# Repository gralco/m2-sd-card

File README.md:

# m2-sd-card

M.2 Key E MicroSD card board for the Librem 5. Using a NXP NVT4857UK, TI TXS0206, Diodes Inc. PI4ULS3V4857 SD 3.0-SDR104 compliant bidirectional level translator.

The contents of this repo is licensed under the GNU GPLv3+

### Manufacturing details

The board should be 0.8mm thick. Make sure you select the "Gold fingers" option when ordering.

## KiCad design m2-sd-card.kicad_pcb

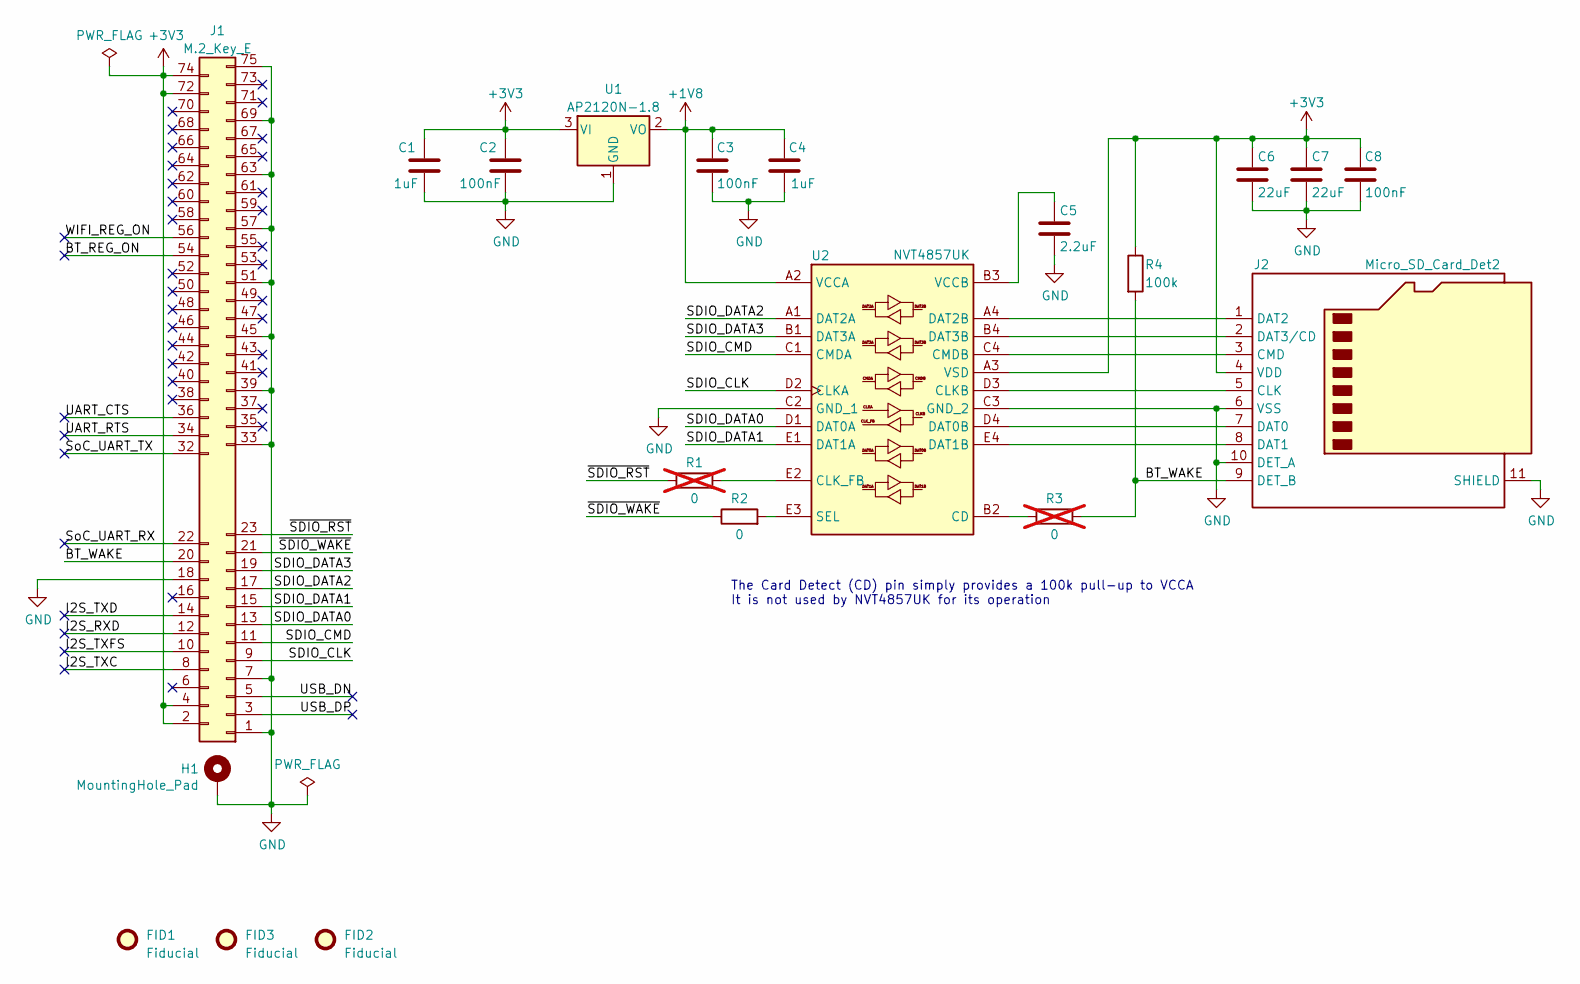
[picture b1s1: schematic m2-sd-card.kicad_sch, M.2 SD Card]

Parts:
C1, C4: 1uF; C_0402_1005Metric; Tolerance 10%; MFG Part Num CL05A105KO5NNNC
C2, C3, C8: 100nF; C_0402_1005Metric; Tolerance 10%; MFG Part Num CL05A104KA5NNNC
C5: 2.2uF; C_0402_1005Metric; Tolerance 20%; MFG Part Num CL05A225MQ5NNNC
C6, C7: 22uF; C_0402_1005Metric; Tolerance 20%; MFG Part Num CM05X5R226M06AH080
FID1, FID2, FID3: Fiducial; Fiducial_0.5mm_Mask1mm
H1: MountingHole_Pad; M.2_Mounting_Hole
J1: M.2_Key_E; M.2_Key_E_Gold_Fingers
J2: Micro_SD_Card_Det2; microSD_HC_Hirose_DM3AT-SF-PEJM5; MFG Part Num DM3AT-SF-PEJM5
R1, R3: 0; R_0402_1005Metric; MFG Part Num CRCW04020000Z0EDC; not fitted
R2: 0; R_0402_1005Metric; MFG Part Num CRCW04020000Z0EDC
R4: 100k; R_0402_1005Metric; Tolerance 1%; MFG Part Num ERJ-2RKF1003X
U1: AP2120N-1.8; SOT-23; MFG Part Num AP2120N-1.8TRG1
U2: NVT4857UK; MFG Part Num NVT4857UKAZ

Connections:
+1V8: C3.1, C4.1, U1.2 (VO), U2.A2 (VCCA)
+3V3: C1.1, C2.1, C6.1, C7.1, C8.1, J1.2, J1.4, J1.72, J1.74, J2.4 (VDD), R4.1, U1.3 (VI), U2.A3 (VSD)
/BT_REG_ON: J1.54
/BT_WAKE: J1.20, J2.9 (DET_B), R3.2, R4.2
/I2S_RXD: J1.12
/I2S_TXC: J1.8
/I2S_TXD: J1.14
/I2S_TXFS: J1.10
/SDIO_CLK: J1.9, U2.D2 (CLKA)
/SDIO_CMD: J1.11, U2.C1 (CMDA)
/SDIO_DATA0: J1.13, U2.D1 (DAT0A)
/SDIO_DATA1: J1.15, U2.E1 (DAT1A)
/SDIO_DATA2: J1.17, U2.A1 (DAT2A)
/SDIO_DATA3: J1.19, U2.B1 (DAT3A)
/SoC_UART_RX: J1.22
/SoC_UART_TX: J1.32
/UART_CTS: J1.36
/UART_RTS: J1.34
/USB_DN: J1.5
/USB_DP: J1.3
/WIFI_REG_ON: J1.56
/~SDIO_RST: J1.23, R1.1
/~SDIO_WAKE: J1.21, R2.1
GND: C1.2, C2.2, C3.2, C4.2, C5.2, C6.2, C7.2, C8.2, H1.1, J1.1, J1.7, J1.18, J1.33, J1.39, J1.45, J1.51, J1.57, J1.63, J1.69, J1.75, J2.6 (VSS), J2.10 (DET_A), J2.11 (SHIELD), U1.1 (GND), U2.C2 (GND_1), U2.C3 (GND_2)
unnamed: J2.5 (CLK), U2.D3 (CLKB)
unnamed: J2.3 (CMD), U2.C4 (CMDB)
unnamed: J2.7 (DAT0), U2.D4 (DAT0B)
unnamed: J2.8 (DAT1), U2.E4 (DAT1B)
unnamed: J2.1 (DAT2), U2.A4 (DAT2B)
unnamed: J2.2 (DAT3/CD), U2.B4 (DAT3B)
unnamed: R3.1, U2.B2 (CD)
unnamed: R1.2, U2.E2 (CLK_FB)
unnamed: R2.2, U2.E3 (SEL)
unnamed: C5.1, U2.B3 (VCCB)

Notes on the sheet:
The Card Detect (CD) pin simply provides a 100k pull-up to VCCA It is not used by NVT4857UK for its operation

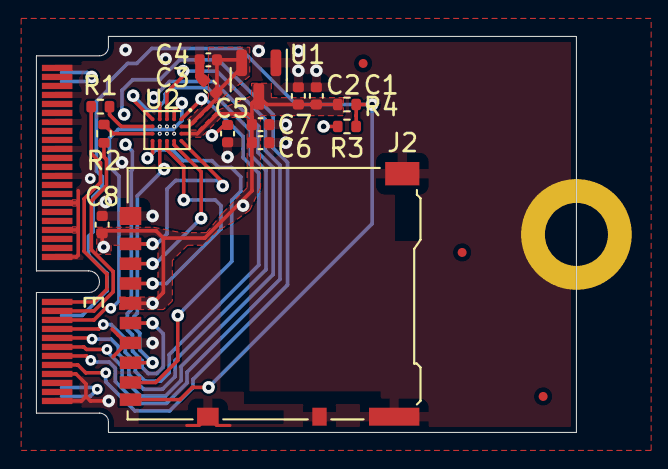
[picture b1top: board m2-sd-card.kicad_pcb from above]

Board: 4 copper layers, 30.0 x 22.0 mm, 20 parts (0 on the bottom side), 22 nets.

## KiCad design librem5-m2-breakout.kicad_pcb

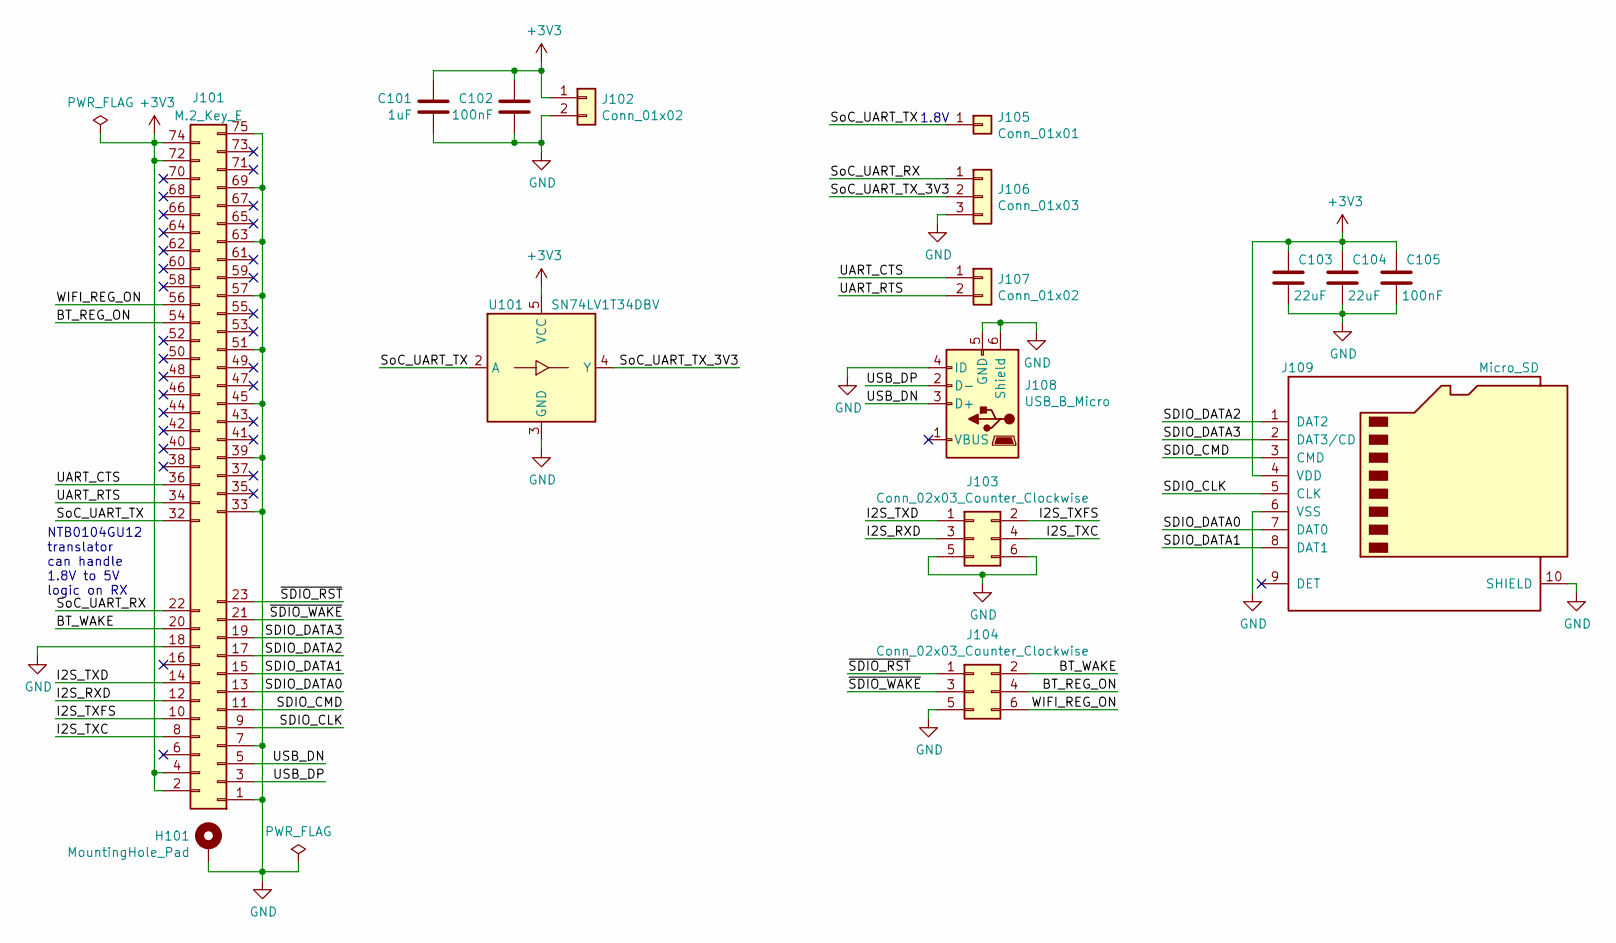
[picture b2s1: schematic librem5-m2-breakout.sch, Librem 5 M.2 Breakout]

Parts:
C101: 1uF; C_0603_1608Metric_Pad1.05x0.95mm_HandSolder
C102, C105: 100nF; C_0603_1608Metric_Pad1.05x0.95mm_HandSolder
C103, C104: 22uF; C_0603_1608Metric_Pad1.05x0.95mm_HandSolder
H101: MountingHole_Pad; M.2_Mounting_Hole
J101: M.2_Key_E; M.2_Key_E_Gold_Fingers
J102: Conn_01x02; PinHeader_1x02_P2.54mm_Vertical; MFG Part Num M20-9990246
J103, J104: Conn_02x03_Counter_Clockwise; PinHeader_2x03_P1.27mm_Vertical_SMD; MFG Part Num 54202-G08-03
J105: Conn_01x01; PinHeader_1x01_P2.54mm_Vertical; MFG Part Num 68000-401HLF
J106: Conn_01x03; PinHeader_1x03_P2.54mm_Vertical; MFG Part Num 61300311121
J107: Conn_01x02; PinHeader_1x02_P1.27mm_Vertical_SMD_Pin1Right
J108: USB_B_Micro; USB_Micro-B_Wuerth_614105150721_Vertical; MFG Part Num 47346-0001
J109: Micro_SD; ALPS_SCHA4B0419; MFG Part Num SCHA4B0419
U101: SN74LV1T34DBV; SOT-23-5_HandSoldering; MFG Part Num SN74LV1T34DBVR

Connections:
+3V3: C101.2, C102.2, C103.2, C104.2, C105.2, J101.2, J101.4, J101.72, J101.74, J102.1, J109.4 (VDD), U101.5 (VCC)
/BT_REG_ON: J101.54, J104.4
/BT_WAKE: J101.20, J104.2
/I2S_RXD: J101.12, J103.3
/I2S_TXC: J101.8, J103.4
/I2S_TXD: J101.14, J103.1
/I2S_TXFS: J101.10, J103.2
/SDIO_CLK: J101.9, J109.5 (CLK)
/SDIO_CMD: J101.11, J109.3 (CMD)
/SDIO_DATA0: J101.13, J109.7 (DAT0)
/SDIO_DATA1: J101.15, J109.8 (DAT1)
/SDIO_DATA2: J101.17, J109.1 (DAT2)
/SDIO_DATA3: J101.19, J109.2 (DAT3/CD)
/SoC_UART_RX: J101.22, J106.1
/SoC_UART_TX: J101.32, J105.1, U101.2 (A)
/SoC_UART_TX_3V3: J106.2, U101.4 (Y)
/UART_CTS: J101.36, J107.1
/UART_RTS: J101.34, J107.2
/USB_DN: J101.5, J108.3 (D+)
/USB_DP: J101.3, J108.2 (D-)
/WIFI_REG_ON: J101.56, J104.6
/~SDIO_RST: J101.23, J104.1
/~SDIO_WAKE: J101.21, J104.3
GND: C101.1, C102.1, C103.1, C104.1, C105.1, H101.1, J101.1, J101.7, J101.18, J101.33, J101.39, J101.45, J101.51, J101.57, J101.63, J101.69, J101.75, J102.2, J103.5, J103.6, J104.5, J106.3, J108.4 (ID), J108.5 (GND), J108.6 (Shield), J109.6 (VSS), J109.10 (SHIELD), U101.3 (GND)

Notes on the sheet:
NTB0104GU12 translator can handle 1.8V to 5V logic on RX
1.8V

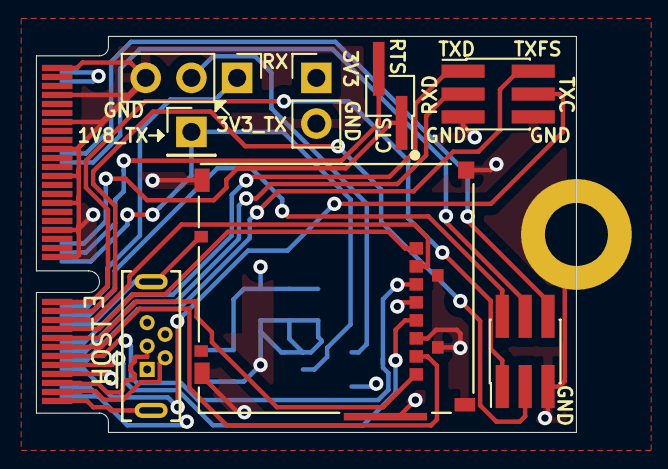
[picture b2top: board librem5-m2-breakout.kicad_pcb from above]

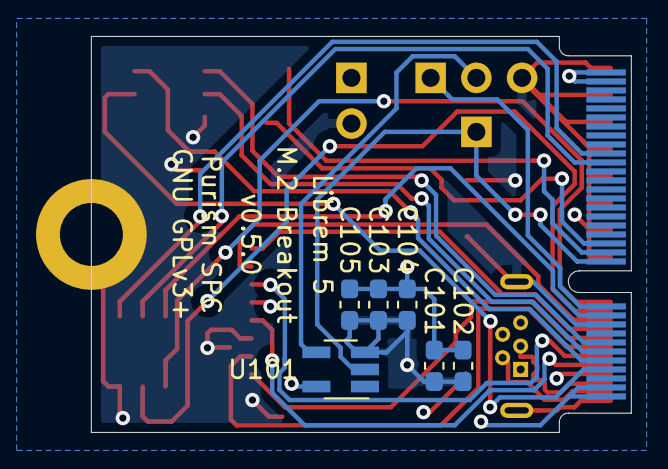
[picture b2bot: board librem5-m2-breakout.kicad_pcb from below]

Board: 4 copper layers, 30.0 x 22.0 mm, 16 parts (6 on the bottom side), 24 nets.

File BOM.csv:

Reference, Value, Footprint, Datasheet, Distrib Link, Distrib PN, MFG Name, MFG Part Num, Others, Tolerance
J102,Conn_01x02,Connector_PinHeader_2.54mm:PinHeader_1x02_P2.54mm_Vertical,~,https://www.digikey.com/product-detail/en/harwin-inc/M20-999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,952-2262-ND,Harwin,M20-9990246,https://www.digikey.com/products/en/connectors-interconnects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,-
C102,100nF,Capacitor_SMD:C_0603_1608Metric_Pad1.05x0.95mm_HandSolder,~,,,,,,
U101,SN74LV1T34DBV,Package_TO_SOT_SMD:SOT-23-5_HandSoldering,http://www.ti.com/lit/ds/symlink/sn74lv1t34.pdf,https://www.digikey.com/product-detail/en/texas-instruments/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,296-37176-1-ND,TI,SN74LV1T34DBVR,https://octopart.com/search?q=SN74LV1T34DBV,-
J109,Micro_SD,m2-sd-card:ALPS_SCHA4B0419,https://www.mouser.com/datasheet/2/15/alps_SCHA4B0419-1155906.pdf,https://www.mouser.com/ProductDetail/ALPS/SCHA4B0419?qs=sGAE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,688-SCHA4B0419,ALPS,SCHA4B0419,https://www.mouser.com/Connectors/Memory-Connectors/Memory-C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|0,-
C105,100nF,Capacitor_SMD:C_0603_1608Metric_Pad1.05x0.95mm_HandSolder,~,,,,,,
C104,22uF,Capacitor_SMD:C_0603_1608Metric_Pad1.05x0.95mm_HandSolder,~,,,,,,
C103,22uF,Capacitor_SMD:C_0603_1608Metric_Pad1.05x0.95mm_HandSolder,~,,,,,,
C101,1uF,Capacitor_SMD:C_0603_1608Metric_Pad1.05x0.95mm_HandSolder,~,,,,,,
J105,Conn_01x01,Connector_PinHeader_2.54mm:PinHeader_1x01_P2.54mm_Vertical,~,https://www.digikey.com/product-detail/en/amphenol-icc-fci/6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,609-3466-ND,Amphenol,68000-401HLF,https://www.digikey.com/products/en/connectors-interconnects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,-
J106,Conn_01x03,Connector_PinHeader_2.54mm:PinHeader_1x03_P2.54mm_Vertical,~,https://www.digikey.com/product-detail/en/w-rth-elektronik/6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,732-5316-ND,Würth Elektronik,61300311121,https://www.digikey.com/products/en/connectors-interconnects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,-
J104,Conn_02x03_Counter_Clockwise,Connector_PinHeader_1.27mm:PinHeader_2x03_P1.27mm_Vertical_SMD,~,https://www.digikey.com/product-detail/en/amphenol-icc-fci/5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,609-5602-ND,Amphenol,54202-G08-03,https://www.digikey.com/products/en/connectors-interconnects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,-
J107,Conn_01x02,Connector_PinHeader_1.27mm:PinHeader_1x02_P1.27mm_Vertical_SMD_Pin1Right,~,https://www.digikey.com/product-detail/en/harwin-inc/M50-363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,952-3933-1-ND,,M50-3630242R,https://www.digikey.com/products/en/connectors-interconnects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,
J108,USB_B_Micro,Connector_USB:USB_Micro-B_Wuerth_614105150721_Vertical,https://www.we-online.de/katalog/datasheet/614105150721.pdf,https://www.digikey.com/product-detail/en/w-rth-elektronik/6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,732-5958-1-ND,Würth Elektronik,614105150721,https://www.mouser.com/ProductDetail/Wurth-Elektronik/614105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,-
J103,Conn_02x03_Counter_Clockwise,Connector_PinHeader_1.27mm:PinHeader_2x03_P1.27mm_Vertical_SMD,~,https://www.digikey.com/product-detail/en/amphenol-icc-fci/5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,609-5602-ND,Amphenol,54202-G08-03,https://www.digikey.com/products/en/connectors-interconnects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,-

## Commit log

2019-12-04 Add all of the project files
2019-12-05 Add board name, version number, and copyright on the back silkscreen
    Removed the paste gerber files since they won't be used.
2019-12-05 Reduce the soldermask clearance from 0.051mm to 0.01mm
    The soldermask dam is no longer being removed in the gerbers.
2019-12-05 Add LICENSE
2019-12-05 Adjust the placement of the RXD and TXC silkscreen text
2019-12-05 Make the USB net class's trace clearance 0.15mm
    The DRC violation that was occuring doesn't realize that the global clearance is less than the diff pair spacing.
2019-12-05 Adjust a couple of traces so they are routed slightly shorted
2019-12-16 Use the Connector:USB_OTG schematic symbol instead of the USB_B_Micro to get rid of the meaningless ERC error due to the "GND" pin being defined as a power output even though it should be defined as 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
    This commit doesn't change anything functionally, hence why the layout is untouched.
2020-01-08 Add bill of materials
2020-02-02 Update the BOM to correctly reflect that the microUSB receptacle is the THT vertical Wurth Elektronik 614105150721
2022-08-19 Add manufacturing details
2023-05-08 Rename the project files to m2-sd-card and make the schematic pass ERC
2023-05-09 Update the schematic to use the NVT4857UK SD 3.0-compliant bidirectional level translator
    Use Hirose DM3AT-SF-PEJM5 for the MicroSD card slot/connector (using
    KiCad's built-in library, with the footprint backed up in the project
    library).
    Add a AP2120N-1.8 1.8V LDO to supply NVT4857UK's VCCA.
    Create the NVT4857UK schematic symbol and footprint.
    Create the AP2120N-18 schematic symbol.
2023-05-09 Fill out the remaining attributes for the passives and export the BOM and schematic as a PDF
2023-05-10 Import all of the footprints into the layout
    Delete the traces and footprints from the M.2 breakout board.
    Update the design rules constraints and physical stackup using PCBWay's
    manufacturing capabilities. These rules should work well for essentially
    any manufacturer that ends up being used.
    Adjust the NVT4857UK's WLCSP20 footprint according to NXP's recommended
    footprint and PCBWay's manufacturing capabilities (allowing for at least
2023-05-11 Hook up all of the nets and make sure DRC is passing
    Exceptions were made for the half-mounting hole and a silkscreen overlap
    with C3.
    Reset the reference designators to first free number starting at 0 so
    that they take up less space on the silkscreen.
    Layout is not completely done and still needs to be polished up.
2023-05-11 Add the calculation for the 50-Ohm single-ended trace width based on PCBWay's 0.8mm 4-layer stackup
2023-05-12 Finish the routing of the board and export the gerbers and all manufacturing files
    Add fab notes to the layout.
    Generate a fabrication drawing and include it in the gerbers directory
    since that is the location PCBWay will use (when this directory's
    contents are archived into a zip).
    Export the 3D step model of the board.
    Export the IPC-D-356 netlist file which will be used to verify the
2023-05-12 Create the board in Horizon EDA by importing the footprints from KiCad so that an ODB++ can be generated for the board
    The project in Horizon does not contain any of the nets, only the
    components since the copper is irrelevant for the PCB assembly.
    Verify that the ODB++ format works as expected using Siemens' ODB++
    viewer.
2023-05-12 Update the readme to describe the m2-sd-card board
2023-05-22 Add the EQ answers and IPC-D-365 files
2023-05-22 Add the panelized gerbers provided by the manufacturer (PCBWay)
2023-05-23 Add the latest EQ question that was answered
2023-05-24 Add a PDF of the layers
2023-05-25 Add an interactive BOM and move the existing BOM to the new bom directory
2023-06-09 Update the reference designators in the BOM to what the should be
    Previously, the designators started at *101 but were shorted to starting
    at *1 so that the text can fit on the silkscreen, but the BOM was not
    updated accordingly (until now).
2023-06-09 Make R1 and R3 DNI in the iBOM, R2 should be populated
2023-06-13 Mark R1 and R3 as "Exclude from bill of materials" in the layout
2024-05-25 Add IPC-2581 file
